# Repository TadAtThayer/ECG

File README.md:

# ECG

Prototype board for our online MENG program.

Utilizes an AD8232 Heart monitor AFE and has a supporting Arduino Nano 33 BLE.

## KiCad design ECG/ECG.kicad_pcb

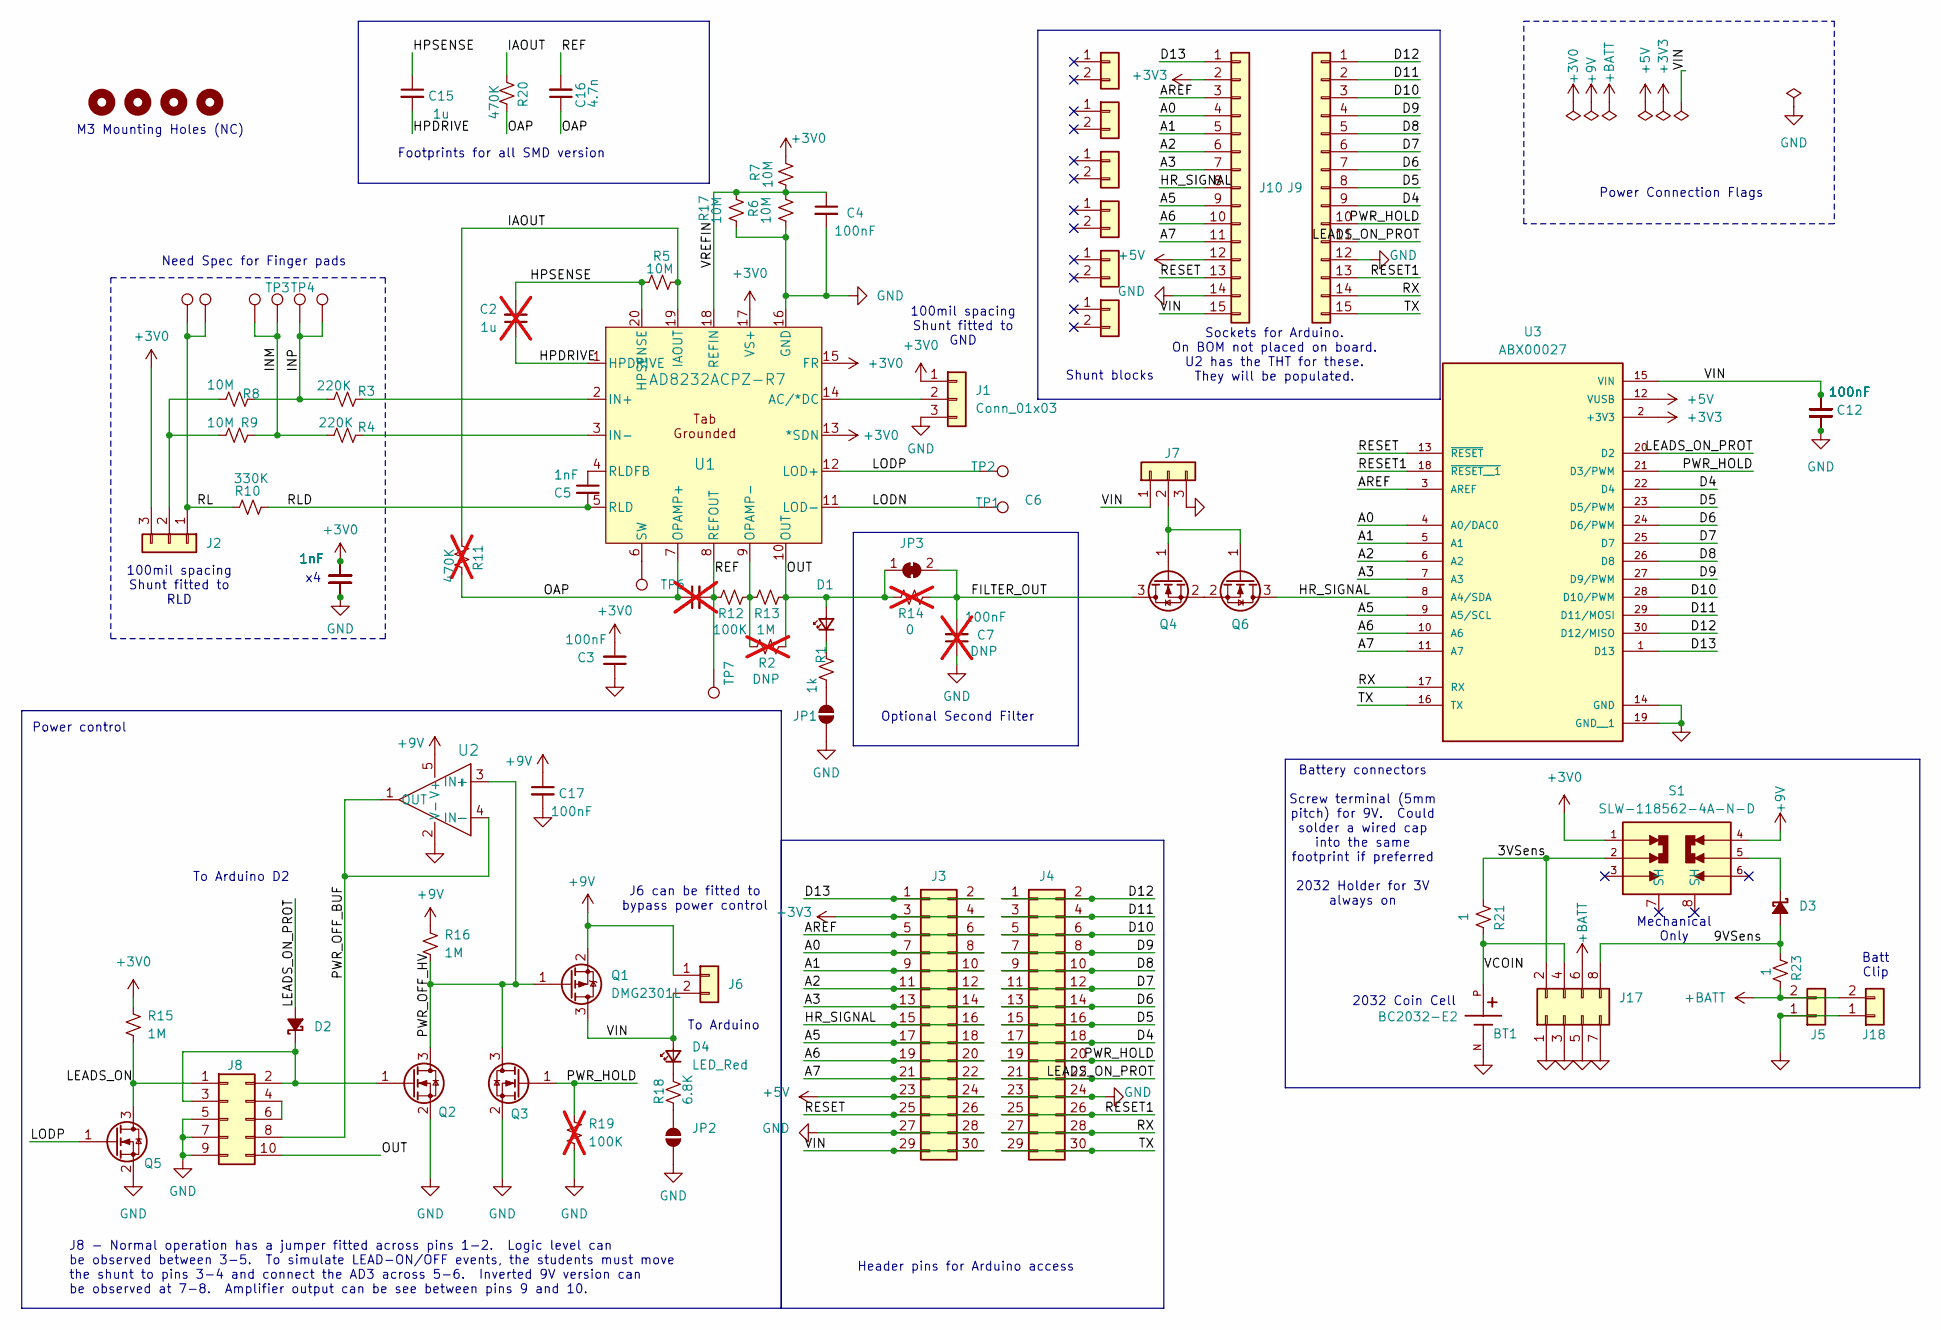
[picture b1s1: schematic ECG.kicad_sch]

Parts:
BT1: BC2032-E2; MPD_BC2032-E2; PARTREV D; DigikeyPN BC2032-E2-ND
C1, C3, C4, C12, C13, C14, C17: 100nF; C_0603_1608Metric; DigikeyPN 1276-1000-1-ND
C2: 1u; C_Rect_L7.2mm_W5.5mm_P5.00mm_FKS2_FKP2_MKS2_MKP2; DigikeyPN 399-5455-1-ND; not fitted
C5, C8, C9, C10, C11: 1nF; C_0603_1608Metric; DigikeyPN 1276-1018-1-ND
C6: 4.7n; C_Rect_L7.2mm_W5.5mm_P5.00mm_FKS2_FKP2_MKS2_MKP2; DigikeyPN 399-5905-ND; not fitted
C7: 100nF; C_Rect_L7.2mm_W5.5mm_P5.00mm_FKS2_FKP2_MKS2_MKP2; not fitted
C15: 1u; C_0603_1608Metric; DigikeyPN 311-2082-1-ND
C16: 4.7n; C_0603_1608Metric; Manufacturer_PN CL10B472KB8NNNC; DigikeyPN 1276-1098-1-ND
D1, D4: LED_Red; LED_0603_1608Metric; MPN 150060RS75000; DigikeyPN 732-4978-2-ND
D2, D3: D_SOD-123; DigikeyPN SM5817PL-TPMSCT-ND
H2, H3, H4, H5: MountingHole; MountingHole_3.2mm_M3
J1, J2, J7: Conn_01x03; PinHeader_1x03_P2.54mm_Vertical; DigikeyPN 732-5316-ND
J3, J4: Conn_02x15_Odd_Even; PinHeader_2x15_P2.54mm_Vertical; DigikeyPN 732-5306-ND
J5: Conn_01x02; 691137710002; DigikeyPN 732-10955-ND
J6: Conn_01x02; PinHeader_1x02_P2.54mm_Vertical; DigikeyPN 2057-PH1-02-UA-ND
J8: Conn_02x05_Odd_Even; PinHeader_2x05_P2.54mm_Vertical; DigikeyPN 2057-PH2-10-UA-ND
J9, J10: Socket 1x15; PinSocket_1x15_P2.54mm_Vertical; DigikeyPN PPPC151LFBN-RC
J11, J12, J13, J14, J15, J16: Shunt block; DigikeyPN S9341-ND
J17: Conn_02x04_Odd_Even; PinHeader_2x04_P2.54mm_Vertical; DigikeyPN 2057-PH2-08-UA-ND
J18: Conn_01x02; DigikeyPN 36-232-ND
JP1, JP2: SolderJumper_2_Open; SolderJumper-2_P1.3mm_Open_RoundedPad1.0x1.5mm
JP3: SolderJumper_2_Bridged; SolderJumper-2_P1.3mm_Bridged_RoundedPad1.0x1.5mm
Q1: DMG2301L; SOT-23; DigikeyPN DMG2301L-7DICT-ND
Q2, Q3, Q4, Q5, Q6: T2N7002AK; SOT-23; DigikeyPN T2N7002AKLMCT-ND
R1: 1k; R_0603_1608Metric; DigikeyPN 311-1.00KFRCT-ND
R2: DNP; R_0603_1608Metric; DigikeyPN RMCF0603FT1M00CT-ND; not fitted
R3, R4: 220K; R_0603_1608Metric; DigikeyPN RMCF0603FT220KCT-ND
R5, R6, R7, R8, R9, R17: 10M; R_0603_1608Metric; DigikeyPN 311-10.0MHRCT-ND
R10: 330K; R_0603_1608Metric; DigikeyPN RMCF0603FT330KCT-ND
R11: 470K; R_Axial_DIN0207_L6.3mm_D2.5mm_P2.54mm_Vertical; DigikeyPN 13-MFR-25FTE52-470KCT-ND; not fitted
R12: 100K; R_0603_1608Metric; DigikeyPN RMCF0603FT100KCT-ND
R13, R15, R16: 1M; R_0603_1608Metric; DigikeyPN 311-1.0MGRCT-ND
R14: 0; R_Axial_DIN0207_L6.3mm_D2.5mm_P2.54mm_Vertical; not fitted
R18: 6.8K; R_0603_1608Metric; DigikeyPN RMCF0603FT6K80CT-ND
R19: 100K; R_0603_1608Metric; DigikeyPN RMCF0603FT1M00CT-ND; not fitted
R20: 470K; R_0603_1608Metric; DigikeyPN RMCF0603FT470KCT-ND
R21, R23: 1; R_0603_1608Metric; DigikeyPN 13-RT0603BRD071RLCT-ND
S1: SLW-118562-4A-N-D; SW_SLW-118562-4A-N-D; PARTREV 1.01; DigikeyPN 2223-SLW-118562-4A-N-D-ND
TP1, TP2, TP3, TP4, TP5, TP6, TP7: TestPoint; TestPoint_Keystone_5000-5004_Miniature
TP9: TestPoint; RefPad
TP10, TP11: TestPoint; FingerPad
U1: AD8232ACPZ-R7; CP_20_10_ADI_NOTH; DigikeyPN 505-AD8232ACPZ-R7CT-ND
U2: OPA237NA/3K; SOT-23-5; DigiKeyPN 296-26265-1-ND
U3: ABX00027; DIP30-ArduinoNano

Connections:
+3V0: C3.2, C8.2, C9.2, C10.2, C11.2, J1.1, J2.3, R7.1, R15.1, S1.1, U1.13 (*SDN), U1.15 (FR), U1.17 (VS+)
+3V3: J3.3, J3.4, J10.2, U3.2 (+3V3)
+5V: J3.23, J3.24, J10.12, U3.12 (VUSB)
+9V: C17.1, J6.1, Q1.2 (S), R16.1, S1.4, U2.5 (V+)
+BATT: J5.2, J17.6, J18.2, R23.2
/3VSens: J17.2, R21.1, S1.2
/9VSens: D3.2 (A), J17.8, R23.1
/A0: J3.7, J3.8, J10.4, U3.4 (A0/DAC0)
/A1: J3.9, J3.10, J10.5, U3.5 (A1)
/A2: J3.11, J3.12, J10.6, U3.6 (A2)
/A3: J3.13, J3.14, J10.7, U3.7 (A3)
/A5: J3.17, J3.18, J10.9, U3.9 (A5/SCL)
/A6: J3.19, J3.20, J10.10, U3.10 (A6)
/A7: J3.21, J3.22, J10.11, U3.11 (A7)
/AREF: J3.5, J3.6, J10.3, U3.3 (AREF)
/D4: J4.17, J4.18, J9.9, U3.22 (D4)
/D5: J4.15, J4.16, J9.8, U3.23 (D5/PWM)
/D6: J4.13, J4.14, J9.7, U3.24 (D6/PWM)
/D7: J4.11, J4.12, J9.6, U3.25 (D7)
/D8: J4.9, J4.10, J9.5, U3.26 (D8)
/D9: J4.7, J4.8, J9.4, U3.27 (D9/PWM)
/D10: J4.5, J4.6, J9.3, U3.28 (D10/PWM)
/D11: J4.3, J4.4, J9.2, U3.29 (D11/MOSI)
/D12: J4.1, J4.2, J9.1, U3.30 (D12/MISO)
/D13: J3.1, J3.2, J10.1, U3.1 (D13)
/FILTER_OUT: C7.2, JP3.2 (B), Q4.3 (D), R14.2
/HPDRIVE: C2.1, C15.2, U1.1 (HPDRIVE)
/HPSENSE: C2.2, C15.1, R5.2, U1.20 (HPSENSE)
/HR_SIGNAL: J3.15, J3.16, J10.8, Q6.3 (D), U3.8 (A4/SDA)
/IAOUT: R5.1, R11.2, R20.2, U1.19 (IAOUT)
/INM: R4.1, R9.2, TP3.1, TP10.1
/INP: R3.1, R8.1, TP4.1, TP11.1
/LEADS_ON: J8.1, Q5.3 (D), R15.2
/LEADS_ON_PROT: D2.2 (A), J4.21, J4.22, J9.11, U3.20 (D2)
/LODN: TP1.1, U1.11 (LOD-)
/LODP: Q5.1 (G), TP2.1, U1.12 (LOD+)
/OAP: C6.1, C16.1, R11.1, R20.1, U1.7 (OPAMP+)
/OUT: D1.2 (A), J8.10, JP3.1 (A), R2.2, R13.2, R14.1, U1.10 (OUT)
/PWR_HOLD: J4.19, J4.20, J9.10, Q3.1 (G), R19.1, U3.21 (D3/PWM)
/PWR_OFF_BUF: J8.8, U2.1 (OUT), U2.4 (IN-)
/PWR_OFF_HV: Q1.1 (G), Q2.3 (D), Q3.3 (D), R16.2, U2.3 (IN+)
/REF: C6.2, C16.2, R12.1, TP7.1, U1.8 (REFOUT)
/RESET: J3.25, J3.26, J10.13, U3.13 (~RESET)
/RESET1: J4.25, J4.26, J9.13, U3.18 (~RESET__1)
/RL: J2.1, R10.1, TP5.1, TP9.1
/RLD: C5.2, R10.2, U1.5 (RLD)
/RX: J4.27, J4.28, J9.14, U3.17 (RX)
/TX: J4.29, J4.30, J9.15, U3.16 (TX)
/VCOIN: BT1.P, J17.4, R21.2
/VIN: C1.2, C12.2, C13.2, C14.2, D4.2 (A), J3.29, J3.30, J6.2, J7.1, J10.15, Q1.3 (D), U3.15 (VIN)
/VREFIN: C4.1, R6.1, R7.2, R17.1, U1.18 (REFIN)
GND: BT1.N, C1.1, C3.1, C4.2, C7.1, C8.1, C9.1, C10.1, C11.1, C12.1, C13.1, C14.1, C17.2, J1.3, J3.27, J3.28, J4.23, J4.24, J5.1, J7.3, J8.5, J8.7, J8.9, J9.12, J10.14, J17.1, J17.3, J17.5, J17.7, J18.1, JP1.1 (A), JP2.1 (A), Q2.2 (S), Q3.2 (S), Q5.2 (S), R6.2, R17.2, R19.2, U1.16 (GND), U2.2 (V-), U3.14 (GND), U3.19 (GND__1)
unnamed: D1.1 (K), R1.1
unnamed: D2.1 (K), J8.2, J8.3, Q2.1 (G)
unnamed: D3.1 (K), S1.5
unnamed: D4.1 (K), R18.1
unnamed: J1.2, U1.14 (AC/*DC)
unnamed: J2.2, R8.2, R9.1
unnamed: J7.2, Q4.1 (G), Q6.1 (G)
unnamed: J8.4, J8.6
unnamed: JP1.2 (B), R1.2
unnamed: JP2.2 (B), R18.2
unnamed: Q4.2 (S), Q6.2 (S)
unnamed: R3.2, U1.2 (IN+)
unnamed: R4.2, U1.3 (IN-)
unnamed: R2.1, R12.2, R13.1, U1.9 (OPAMP-)
unnamed: C5.1, U1.4 (RLDFB)
unnamed: TP6.1, U1.6 (SW)

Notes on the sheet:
To Arduino
Header pins for Arduino access
Footprints for all SMD version
To Arduino D2
100mil spacing Shunt fitted to RLD
2032 Coin Cell
Battery connectors Screw terminal (5mm pitch) for 9V. Could solder a wired cap into the same footprint if preferred 2032 Holder for 3V always on
J8 - Normal operation has a jumper fitted across pins 1-2. Logic level can be observed between 3-5. To simulate LEAD-ON/OFF events, the students must move the shunt to pins 3-4 and connect the AD3 across 5-6. Inverted 9V version can be observed at 7-8. Amplifier output can be see between pins 9 and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
100mil spacing Shunt fitted to GND
Mechanical Only
J6 can be fitted to bypass power control
Sockets for Arduino. On BOM not placed on board. U2 has the THT for these. They will be populated.
Power Connection Flags
Shunt blocks
Optional Second Filter
Power control
Batt Clip
M3 Mounting Holes (NC)
Need Spec for Finger pads

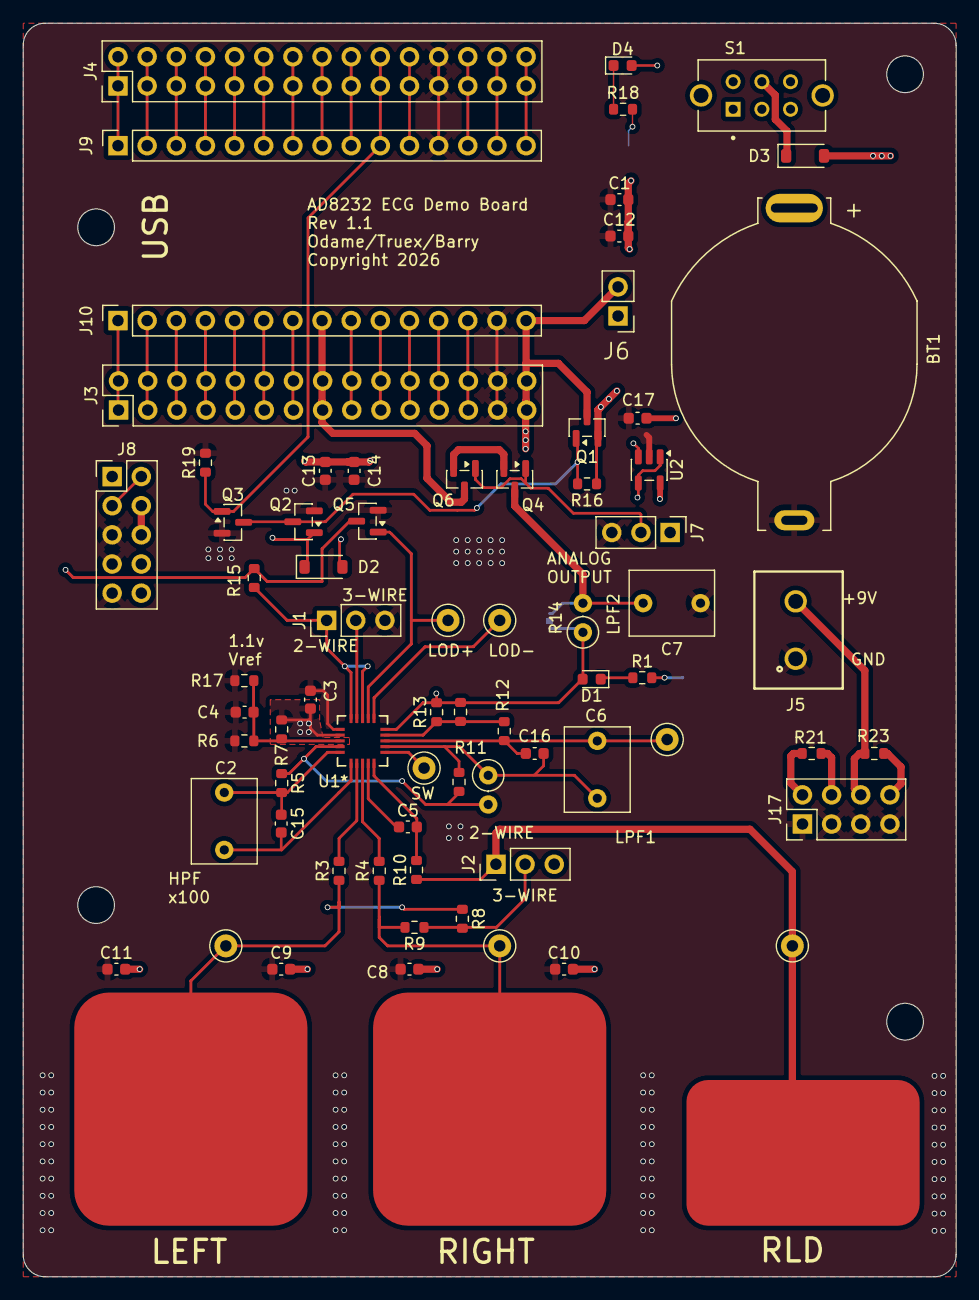
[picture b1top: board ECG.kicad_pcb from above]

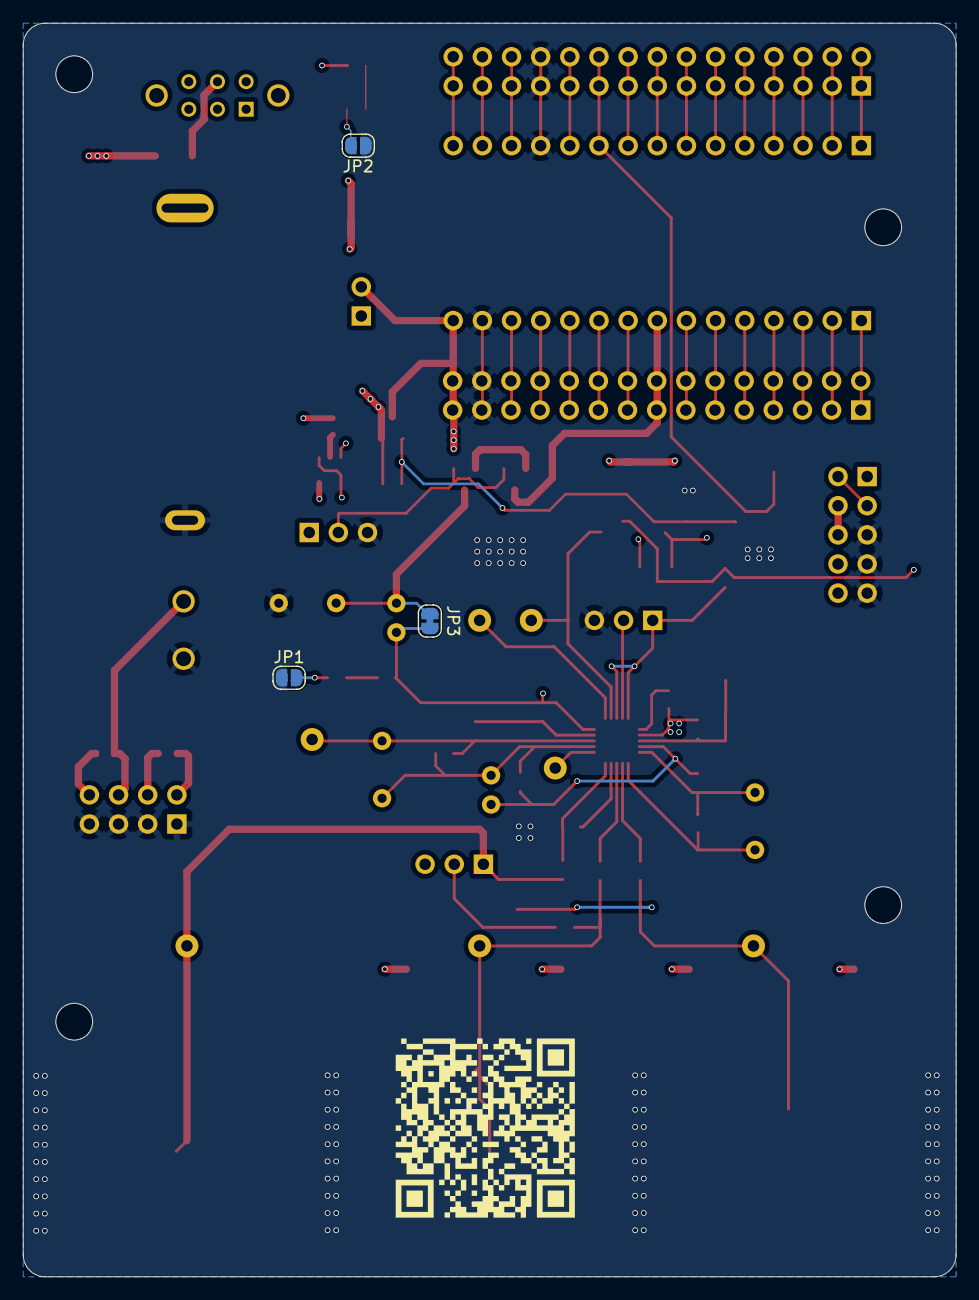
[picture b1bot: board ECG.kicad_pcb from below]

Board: 4 copper layers, 81.3 x 109.2 mm, 81 parts (3 on the bottom side), 68 nets.

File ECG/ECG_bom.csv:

Comment,Designator,Footprint,LCSC Part #
100nF,"C1,C3,C4,C12,C13,C14,C17",Capacitor_SMD:C_0603_1608Metric,C1591
1nF,"C5,C8,C9,C10,C11",Capacitor_SMD:C_0603_1608Metric,C1588
1u,C15,Capacitor_SMD:C_0603_1608Metric,C559769
4.7n,C16,Capacitor_SMD:C_0603_1608Metric,C1621
~,"D2,D3",Diode_SMD:D_SOD-123,C669022
DMG2301L,Q1,Package_TO_SOT_SMD:SOT-23,C102619
T2N7002AK,"Q2,Q3,Q4,Q5,Q6",Package_TO_SOT_SMD:SOT-23,C516175
1k,R1,Resistor_SMD:R_0603_1608Metric,C137393
220K,"R3,R4",Resistor_SMD:R_0603_1608Metric,C2479593
10M,"R5,R6,R7,R8,R9,R17",Resistor_SMD:R_0603_1608Metric,C2930145
330K,R10,Resistor_SMD:R_0603_1608Metric,C4196069
100K,R12,Resistor_SMD:R_0603_1608Metric,C237792
1M,"R13,R15,R16",Resistor_SMD:R_0603_1608Metric,C107698
6.8K,R18,Resistor_SMD:R_0603_1608Metric,C2479438
470K,R20,Resistor_SMD:R_0603_1608Metric,C2484678
1,"R21,R23",Resistor_SMD:R_0603_1608Metric,C1857704
AD8232ACPZ-R7,U1,ECG_Footprints:CP_20_10_ADI_NOTH,C43216
OPA237NA/3K,U2,Package_TO_SOT_SMD:SOT-23-5,C90349

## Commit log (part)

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2025-07-21 Add skeleton Kicad Proj
    Add a few words in the readme.
2025-07-21 start collecting footprints and docs
2025-07-22 WIP - Bobs V1 more or less captured.
2025-07-23 use NO4 as inverter
2025-07-23 begin assigning footprints
2025-07-23 first pass transistor based power control
2025-07-24 add battery connections and start playing with placement
2025-07-24 WIP Transitor Switches
    Work on transistor placement
2025-07-24 tinkering with switching logic placements
2025-07-24 WIP
    first edits
2025-07-24 WIP2
    new positions
2025-07-25 WIPmorning1
    switch added
2025-07-25 WIPmorn2
    SBD
2025-07-25 R22
    want layout update
2025-07-25 Vref?
    Vref layout wrong
2025-07-25 Done for Friday
    See you Monday. Parts connected and snugged up.
2025-07-28 Vref, add TPs
    Added R17, TP7, TP8
2025-07-28 Labels
    Added all labels
2025-07-29 start cleanup
2025-07-30 WIP:
    1) Cleanup macro placement a bit to reduce board cost.
    2) Start final routing and plane additions
    3) Clean up drcs.
2025-07-30 DRC and ERC clean.
    Decent layout.
    Silk needs work.
2025-07-30 V1.0 candidate
2025-07-31 getting close. Larger vias for cheaper process
2025-07-31 Edits from review with Kofi
2025-07-31 Add strain relief
2025-08-01 final tweaks for v1.0
    Add protection diode for Arduino D2
    Add some silk
2025-08-01 fix qrcode
2025-08-01 Fix +9V Label
2025-08-01 Work on BOM
2025-08-05 BOM updates.
2025-08-08 Start cleaning up fab layers for build
2025-08-14 Connect IAOUT to R11. Disconnect Disconnect Pin 1 from R11
    Fixes #6
2025-08-27 officially DNP one of the otional caps
2025-09-08 Add some mounting holes
    Close #3
2025-09-08 silkscreen cleanup
2025-09-08 Remove thermal pad and pin from ADI HRM chip. Doesn't provide any obvious benefit and make manual assembly very difficult.
    Close #9
2025-09-08 add some SMD footprint for SMD only version
    Close #10
2025-09-08 Update rev number and logo
    Close #11
2025-09-08 gerbers for v1.0b
2025-09-15 add samd21 data sheet
2025-10-03 start pruning
2025-10-09 add tracer
2025-12-11 Register some ECOs on the schematic.
    Implementation still TBD
2025-12-16 Change coin cell holder to one the is dummy "proof"
    Close #14
2025-12-16 Add control of LeadsOn from AD3
    Close #16
2025-12-22 new diode footprint
2026-01-09 Work on AD3 connection stuff
2026-01-12 Manually merge commit d0bb662.
    Low leakage schottky for protection.
2026-01-12 cleanup layout
2026-01-12 Cleanup layout.
    Close #17
    Close #15
2026-01-12 update qr code
2026-01-12 work on manufacturing
2026-01-16 Remove paste from finger pads.
    new gerbers
2026-01-16 Update bom and placement files for manufacturing
    Changes to be committed:
    modified: ECG-top-pos.csv
    modified: ECG.csv
    modified: ECG_bom.csv
2026-01-27 wip bom
2026-01-27 annotations for manual thd comps
2026-06-03 Replace 3 THD comps with the SMD versions in the callout box.
    Remove old revision tracker.
    Fix latent overlapping silkscreen error.
2026-06-17 Add J7 and Q6.
    J7 allows the students to turn off the path to the output of the 8232.
    Q6 provides a second reversed body diode on the path to prevent
    current flow when the path is blocked via the jumper and the
    students force a voltage onto A4.
    Close #20.
2026-06-17 Add a connector for testing supply voltages.
    Close #27
    Close #28
2026-06-18 add R21 and R23 for current measurement
2026-06-18 Add 1 ohm resistors to both supplies for current measurement (R21 R23).
    Update J17 to provide test points for both.
    Close #23
    Close #24
2026-06-23 Add double row header pins for Arduino. BOM not yet updated.
    Close #26
2026-06-23 Add op amp buffer to pwr_off_hv to allow monitoring with the relatively low input impedance of the AD3
    Work on #25
    Probably need to look for a CMOS op-amp. This one pulls
    600nA input bias which will likely turn on the pfet and
    power up the nano all the time...
2026-06-29 Start looking at footprints and placements.

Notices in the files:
ECG/ECG.kicad_pcb:
Copyright 2026
